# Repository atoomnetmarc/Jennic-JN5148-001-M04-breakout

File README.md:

Yes, the JN5148-001-M04 module is old. NXP has professionally erased all documents and software from their website except for the [product brief](https://www.nxp.com/products/no-longer-manufactured/32-bit-mcu-and-ieee802-15-4-transceiver:JN5148).

However, I have some JN5148-001-M04 modules and want to play with them. So I created this crude breakout board.

# Assembly instructions

Solder all components except the module. Clean PCB.

Test if 3V3 regulator works by connecting 5V (with 50mA power limit). The board should not use any significant current. Measure the 3V3 OUT-pin, it should be 3.3V.

Now solder module.

# Test programming mode

Use 'NXP JN51xx Flash Programmer 1.8.9'. Connect a 3.3V serial to USB converter (like a FT232RL) and put Jennic module into program mode by pressing and holding PGM while short pressing RST.\
When selecting a COM Port the programming software should identify the device type, flash chip and MAC Address.

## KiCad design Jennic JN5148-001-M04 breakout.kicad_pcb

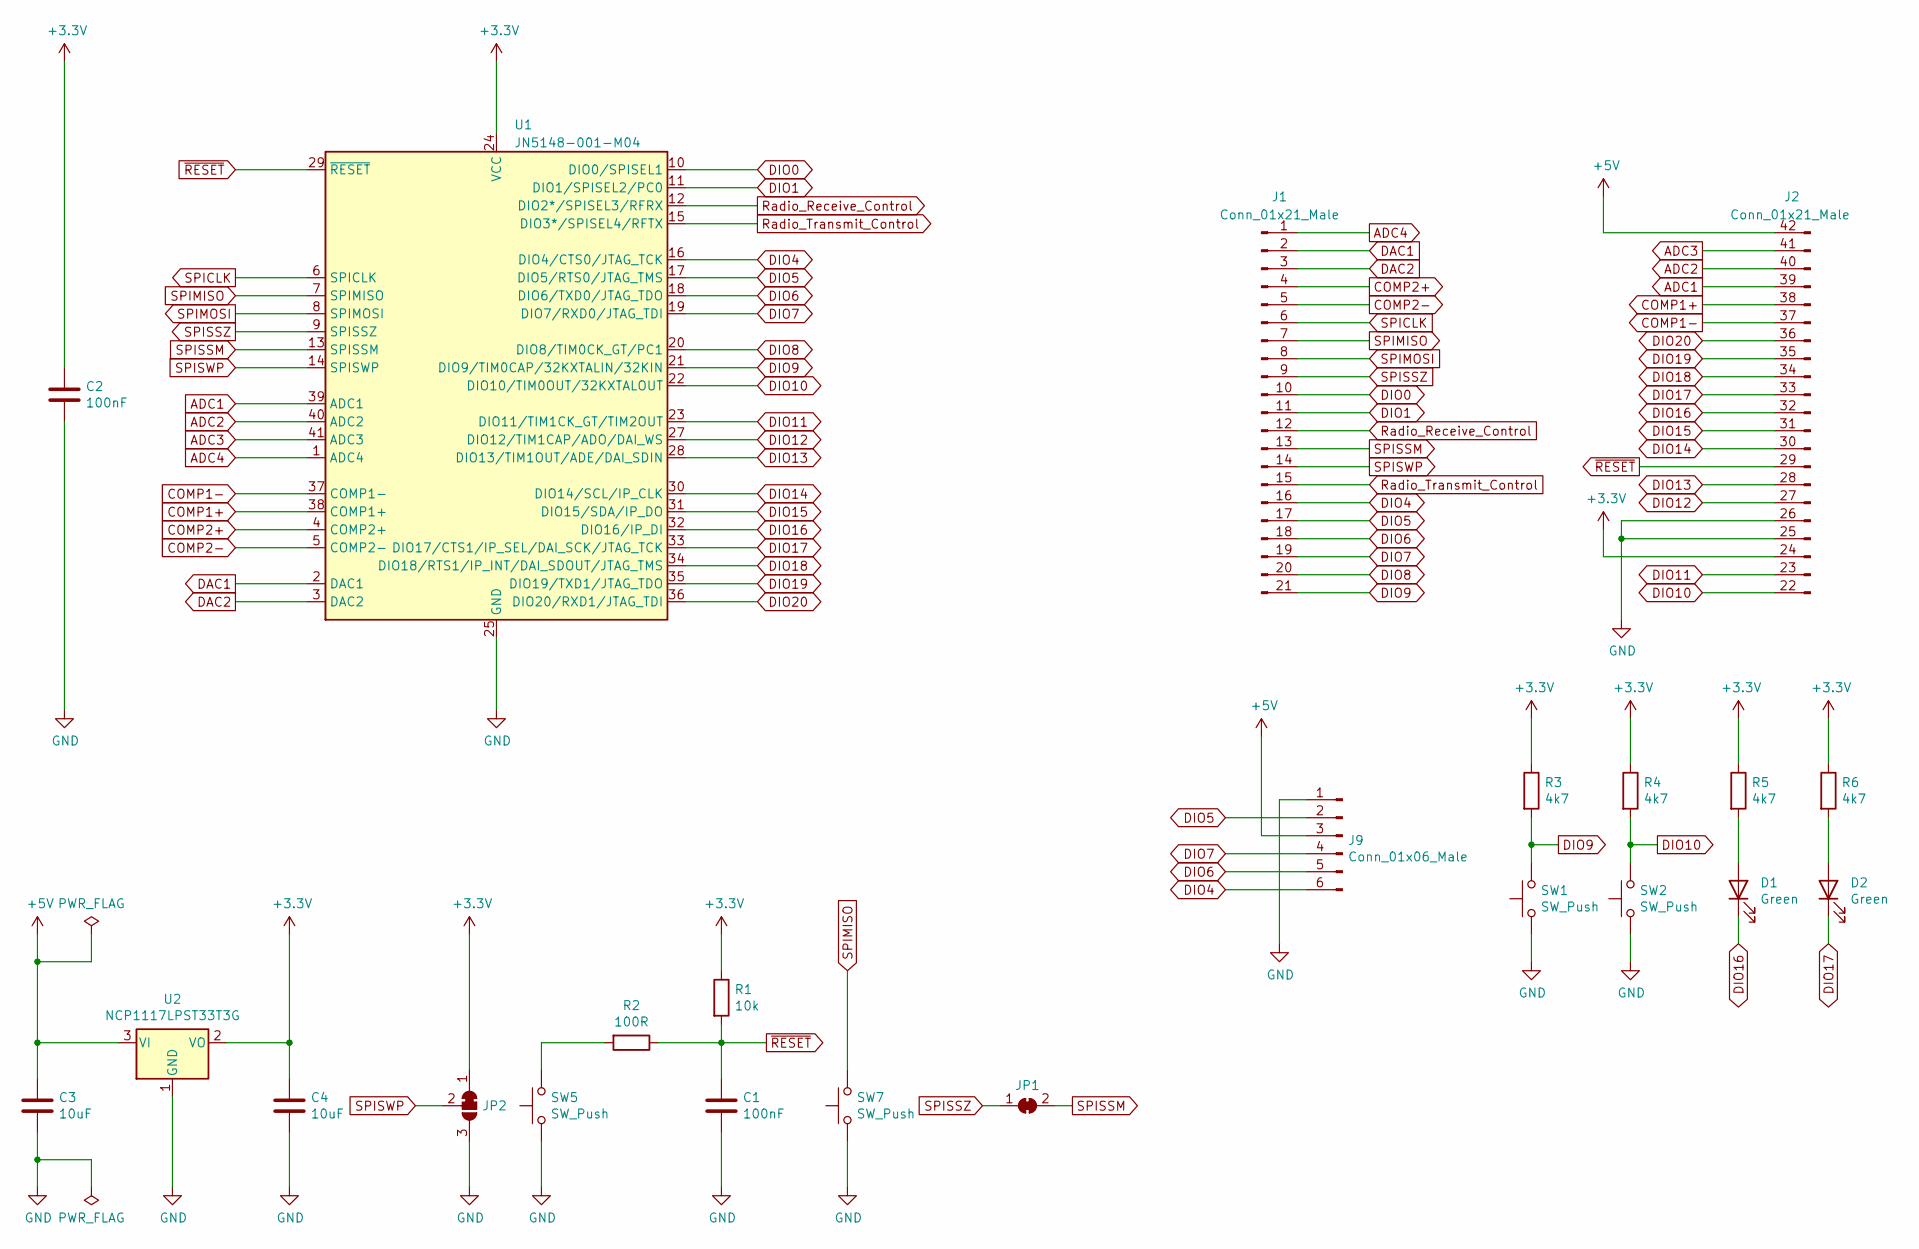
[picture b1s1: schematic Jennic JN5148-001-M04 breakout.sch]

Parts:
C1, C2: 100nF; C_0805_2012Metric_Pad1.18x1.45mm_HandSolder
C3, C4: 10uF; C_0805_2012Metric_Pad1.18x1.45mm_HandSolder
D1, D2: Green; LED_0805_2012Metric_Pad1.15x1.40mm_HandSolder
J1: Conn_01x21_Male; PinHeader_1x21_P2.54mm_Vertical
J2: Conn_01x21_Male; PinHeader_1x21+21_P2.54mm_Vertical
J9: Conn_01x06_Male; PinHeader_1x06_P2.54mm_Horizontal
JP1: SolderJumper_2_Bridged; SolderJumper-2_P1.3mm_Bridged_RoundedPad1.0x1.5mm
JP2: SolderJumper_3_Bridged12; SolderJumper-3_P1.3mm_Bridged12_RoundedPad1.0x1.5mm
R1: 10k; R_0805_2012Metric_Pad1.20x1.40mm_HandSolder
R2: 100R; R_0805_2012Metric_Pad1.20x1.40mm_HandSolder
R3, R4, R5, R6: 4k7; R_0805_2012Metric_Pad1.20x1.40mm_HandSolder
SW1, SW2, SW5, SW7: SW_Push; SW_SPST_CK_RS282G05A3
U1: JN5148-001-M04; JN5148-001-M04-handsolder
U2: NCP1117LPST33T3G; SOT-223-3_TabPin2

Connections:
+3V3: C2.1, C4.1, J2.24 (Pin_3), JP2.1 (A), R1.1, R3.1, R4.1, R5.1, R6.1, U1.24 (VCC), U2.2 (VO)
+5V: C3.1, J2.42 (Pin_21), J9.3, U2.3 (VI)
ADC1: J2.39 (Pin_18), U1.39 (ADC1)
ADC2: J2.40 (Pin_19), U1.40 (ADC2)
ADC3: J2.41 (Pin_20), U1.41 (ADC3)
ADC4: J1.1, U1.1 (ADC4)
COMP1+: J2.38 (Pin_17), U1.38 (COMP1+)
COMP1-: J2.37 (Pin_16), U1.37 (COMP1-)
COMP2+: J1.4, U1.4 (COMP2+)
COMP2-: J1.5, U1.5 (COMP2-)
DAC1: J1.2, U1.2 (DAC1)
DAC2: J1.3, U1.3 (DAC2)
DIO0: J1.10, U1.10 (DIO0/SPISEL1)
DIO1: J1.11, U1.11 (DIO1/SPISEL2/PC0)
DIO4: J1.16, J9.6, U1.16 (DIO4/CTS0/JTAG_TCK)
DIO5: J1.17, J9.2, U1.17 (DIO5/RTS0/JTAG_TMS)
DIO6: J1.18, J9.5, U1.18 (DIO6/TXD0/JTAG_TDO)
DIO7: J1.19, J9.4, U1.19 (DIO7/RXD0/JTAG_TDI)
DIO8: J1.20, U1.20 (DIO8/TIM0CK_GT/PC1)
DIO9: J1.21, R3.2, SW1.2, U1.21 (DIO9/TIM0CAP/32KXTALIN/32KIN)
DIO10: J2.22 (Pin_1), R4.2, SW2.2, U1.22 (DIO10/TIM0OUT/32KXTALOUT)
DIO11: J2.23 (Pin_2), U1.23 (DIO11/TIM1CK_GT/TIM2OUT)
DIO12: J2.27 (Pin_6), U1.27 (DIO12/TIM1CAP/ADO/DAI_WS)
DIO13: J2.28 (Pin_7), U1.28 (DIO13/TIM1OUT/ADE/DAI_SDIN)
DIO14: J2.30 (Pin_9), U1.30 (DIO14/SCL/IP_CLK)
DIO15: J2.31 (Pin_10), U1.31 (DIO15/SDA/IP_DO)
DIO16: D1.1 (K), J2.32 (Pin_11), U1.32 (DIO16/IP_DI)
DIO17: D2.1 (K), J2.33 (Pin_12), U1.33 (DIO17/CTS1/IP_SEL/DAI_SCK/JTAG_TCK)
DIO18: J2.34 (Pin_13), U1.34 (DIO18/RTS1/IP_INT/DAI_SDOUT/JTAG_TMS)
DIO19: J2.35 (Pin_14), U1.35 (DIO19/TXD1/JTAG_TDO)
DIO20: J2.36 (Pin_15), U1.36 (DIO20/RXD1/JTAG_TDI)
GND: C1.2, C2.2, C3.2, C4.2, J2.25 (Pin_4), J2.26 (Pin_5), J9.1, JP2.3 (B), SW1.1, SW2.1, SW5.1, SW7.1, U1.25 (GND), U1.26 (GNDA), U2.1 (GND)
unnamed: D1.2 (A), R5.2
unnamed: D2.2 (A), R6.2
unnamed: R2.2, SW5.2
Radio_Receive_Control: J1.12, U1.12 (DIO2*/SPISEL3/RFRX)
Radio_Transmit_Control: J1.15, U1.15 (DIO3*/SPISEL4/RFTX)
SPICLK: J1.6, U1.6 (SPICLK)
SPIMISO: J1.7, SW7.2, U1.7 (SPIMISO)
SPIMOSI: J1.8, U1.8 (SPIMOSI)
SPISSM: J1.13, JP1.2 (B), U1.13 (SPISSM)
SPISSZ: J1.9, JP1.1 (A), U1.9 (SPISSZ)
SPISWP: J1.14, JP2.2 (C), U1.14 (SPISWP)
~RESET: C1.1, J2.29 (Pin_8), R1.2, R2.1, U1.29 (~RESET)

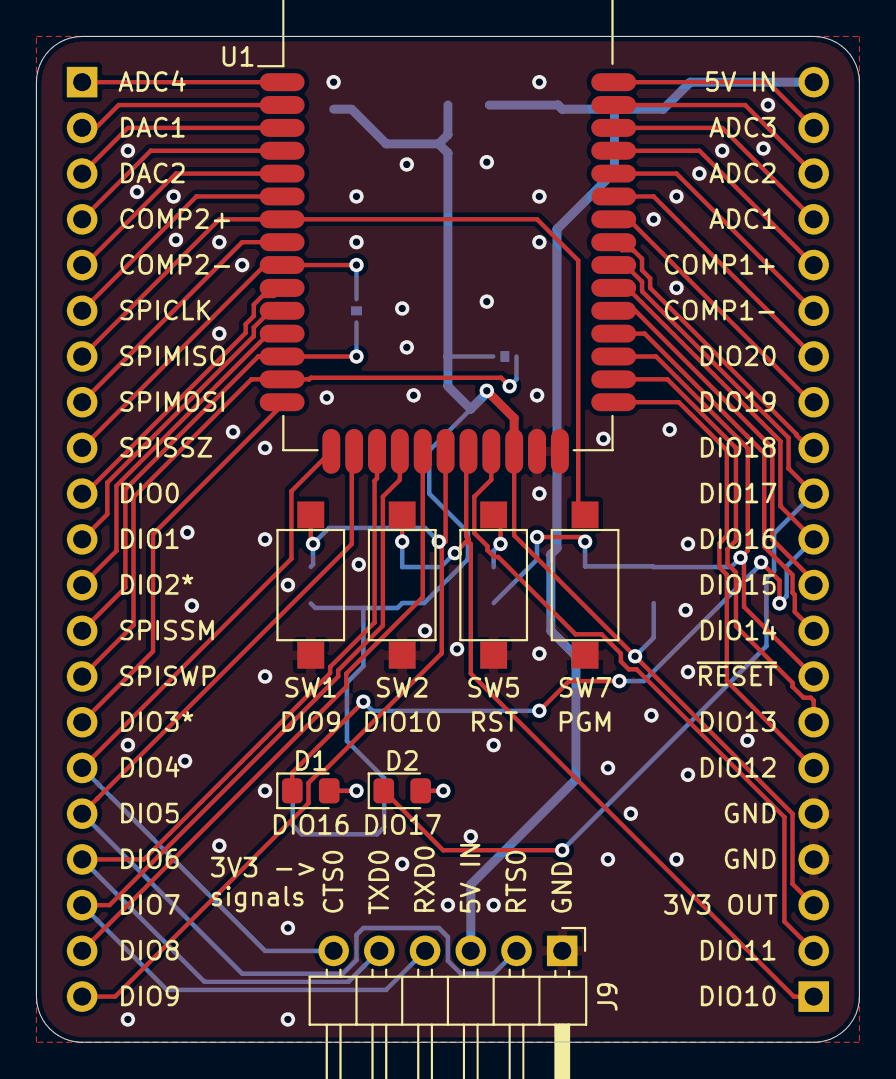
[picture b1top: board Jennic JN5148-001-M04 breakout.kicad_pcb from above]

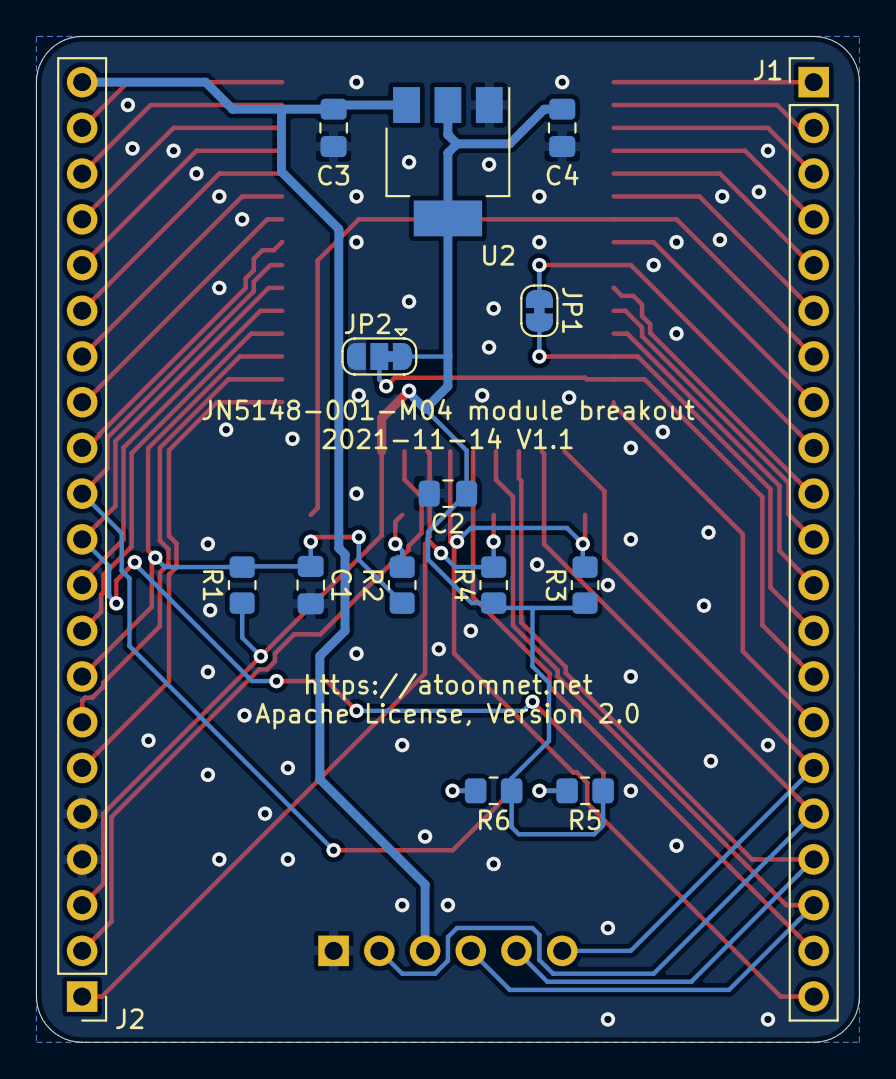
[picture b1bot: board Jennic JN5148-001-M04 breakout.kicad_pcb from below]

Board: 2 copper layers, 45.7 x 55.9 mm, 23 parts (15 on the bottom side), 44 nets.

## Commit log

2021-11-14 Aligned resistor R3.

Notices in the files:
Jennic JN5148-001-M04 breakout.kicad_pcb:
Apache License, Version 2.0
README.md:
License: Apache 2.0
